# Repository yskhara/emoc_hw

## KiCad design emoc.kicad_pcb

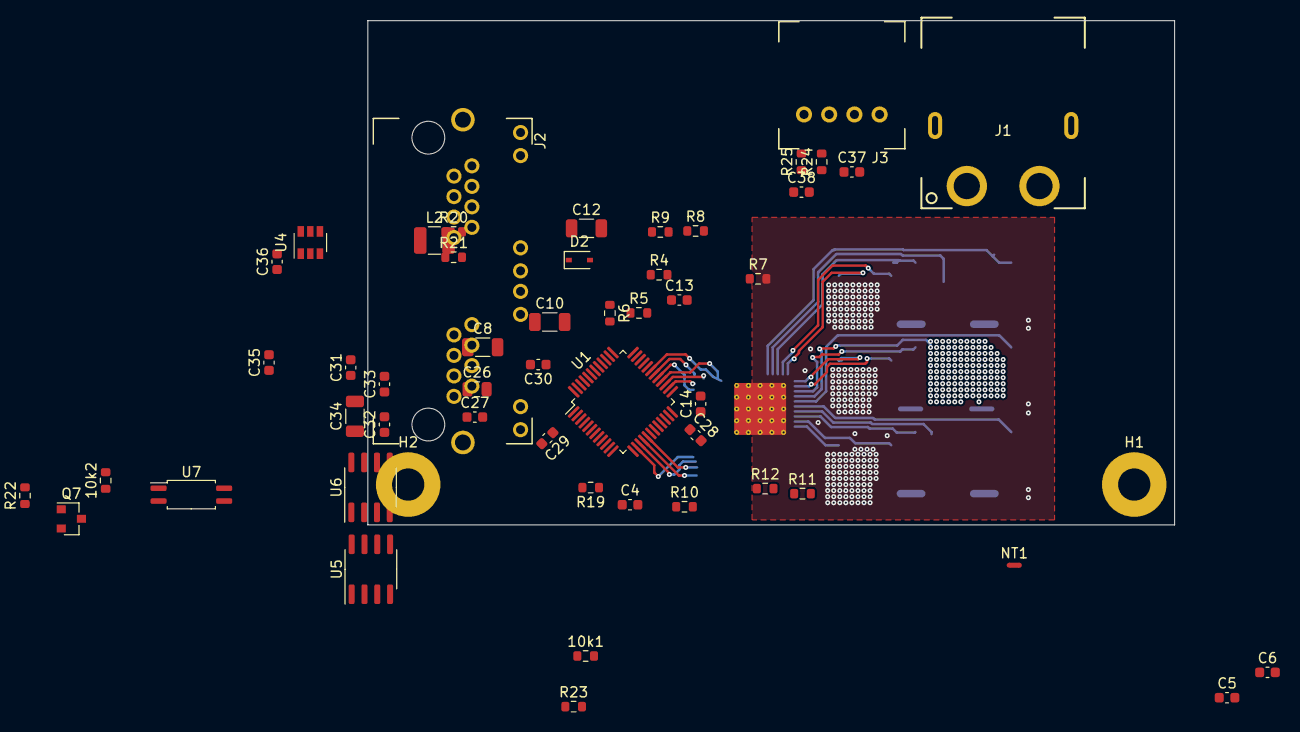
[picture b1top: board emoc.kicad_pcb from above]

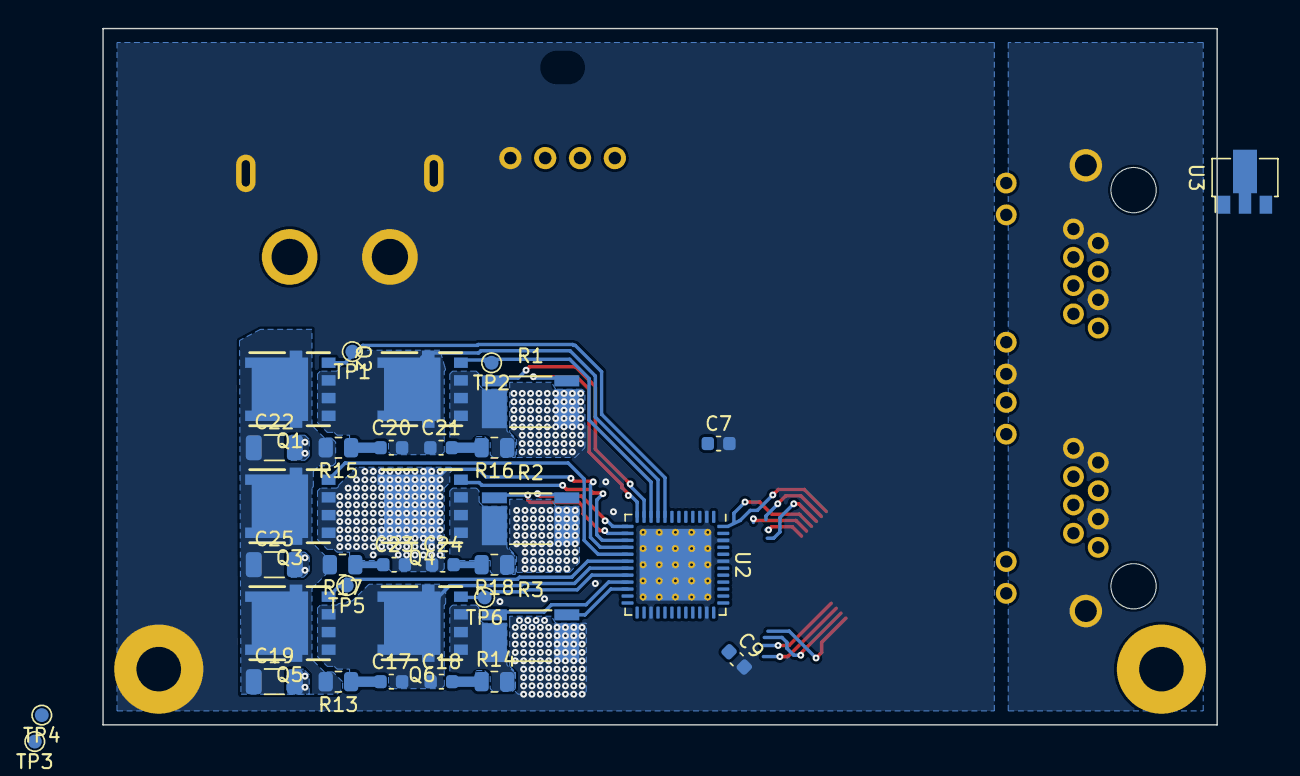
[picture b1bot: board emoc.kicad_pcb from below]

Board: 4 copper layers, 80.0 x 50.0 mm, 87 parts (34 on the bottom side), 81 nets.

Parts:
10k1, 10k2: R_US; R_0603_1608Metric
C4, C5, C6: TBD; C_0603_1608Metric
C7, C9, C14, C28, C29, C30, C31, C32, C33, C35, C36: 100n; C_0603_1608Metric
C8, C12, C34: 1u; C_1206_3216Metric
C10: 4.7uF; C_1206_3216Metric
C13: 47n; C_0603_1608Metric
C17, C18, C20, C21, C23, C24: 4n7; C_0603_1608Metric
C19, C22, C25: TBD; C_1206_3216Metric
C26: 1u; C_0805_2012Metric
C27: 10n; C_0603_1608Metric
C37, C38: 220p; C_0603_1608Metric
D2: PMEG6010CEJ,115; D_SOD-323
H1, H2: MountingHole_Pad; MountingHole_3.2mm_M3_Pad
J1: XT60PW-M
J2: RJHSE-x38x-02_CAN; RJHSE-x38x-02
J3: Conn_01x04; EP25_1744426-4
L2: L; L_1210_3225Metric
NT1: Net-Tie_2; NetTie-2_SMD_Pad0.5mm
Q1, Q2, Q3, Q4, Q5, Q6: NVMFS5C604NL; SO-8FL
Q7: BSS138; SOT-23
R1, R2, R3: R_Shunt_US; R_Shunt_2512
R4, R7, R19: 10k; R_0603_1608Metric
R5, R10, R11, R12: TBD; R_0603_1608Metric
R6, R8, R9: 54k9; R_0603_1608Metric
R13, R14, R15, R16, R17, R18: 10; R_0805_2012Metric
R20, R21: R_US; R_0603_1608Metric
R22, R24, R25: 100R; R_0603_1608Metric
R23: 51k1; R_0603_1608Metric
TP1, TP2, TP3, TP4, TP5, TP6: TestPoint; TestPoint_Pad_D1.0mm
U1: STM32F303CBTx; LQFP-48_7x7mm_P0.5mm
U2: DRV8323R; VQFN-48-1EP_7x7mm_P0.5mm_EP5.15x5.15mm_ThermalVias
U3: MC78L05_SOT89; SOT-89-3
U4: TPS562201; SOT-23-6
U5: Si8621AB-B-IS; SOIC-8_3.9x4.9mm_P1.27mm
U6: NCV7351D13; SOIC-8_3.9x4.9mm_P1.27mm
U7: TLP291; SOIC-4_4.55x2.6mm_P1.27mm

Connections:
+3V3: C28.1, C29.1, C30.1, R4.1, R19.2, U1.1, U1.24, U1.36, U1.48, U5.1, U7.4
+5V: J3.2, R6.1
+5VD: C33.1, C34.1, C35.1, C36.1, L2.2, R20.2, U3.1, U5.8, U6.3, U6.5
+12V: 10k2.2, C31.2, J2.1-4, J2.1-5, J2.2-4, J2.2-5, U3.3, U4.3, U4.5
/emoc_page3/SL_A: Q2.1, Q2.2, Q2.3, R1.1, R16.1
/emoc_page3/SL_B: Q4.1, Q4.2, Q4.3, R2.1, R18.1
/emoc_page3/SL_C: Q6.1, Q6.2, Q6.3, R3.1, R14.1
/emoc_page4/CAN_H: J2.1-1, J2.2-1, U6.7
/emoc_page4/CAN_L: J2.1-2, J2.2-2, U6.6
/emoc_page4/~EMS_ISO: J2.1-6, J2.2-6, R22.2, R23.1
CAN_RX: U1.45, U5.3
CAN_TX: U1.46, U5.2
DC_FB: R8.1, R9.2
ENC_A: C37.2, R24.1
ENC_B: C38.1, R25.1
FAULT: R4.2, U2.28
GH_A: Q1.4, TP1.1, U2.8
GH_B: Q3.4, TP3.1, U2.17
GH_C: Q5.4, TP5.1, U2.18
GL_A: Q2.4, TP2.1, U2.10
GL_B: Q4.4, TP4.1, U2.15
GL_C: Q6.4, TP6.1, U2.20
GND: 10k1.1, C4.2, C5.2, C6.2, C7.2, C8.2, C9.2, C10.2, C19.2, C22.2, C25.2, C26.2, C27.2, C28.2, C29.2, C30.2, C37.1, C38.2, H1.1, H2.1, J1.1, J1.3, J3.1, R1.4, R2.4, R3.4, R7.2, R9.1, U1.23, U1.35, U1.47, U2.2, U2.27, U2.35, U2.43, U2.46, U2.49, U5.4
GNDD: C31.1, C33.2, C34.2, C35.2, C36.2, J2.1-3, J2.1-7, J2.1-8, J2.2-3, J2.2-7, J2.2-8, J2.2-9, J2.S1, J2.S2, Q7.2, R21.1, R23.2, U3.2, U4.1, U5.5, U6.2, U6.8
IA: C6.1, R12.2
IB: C5.1, R11.2
IC: C4.1, R10.2
INH_A: U1.29, U2.37
INH_B: U1.30, U2.39
INH_C: U1.31, U2.41
INL_A: U1.26, U2.38
INL_B: U1.27, U2.40
INL_C: U1.28, U2.42
MISO: U1.16, U2.29
MOSI: U1.17, U2.30
unnamed: 10k2.1, U7.1
unnamed: C8.1, U2.36
unnamed: C7.1, C10.1, C12.1, D2.1, U2.6
unnamed: C12.2, U2.5
unnamed: C13.1, U2.4
unnamed: C13.2, U2.3
unnamed: C14.1, U2.44
unnamed: C14.2, U2.45
unnamed: C17.1, R13.1
unnamed: C18.2, R14.2
unnamed: C20.1, R15.1
unnamed: C21.2, R16.2
unnamed: C23.1, R17.1
unnamed: C24.2, R18.2
unnamed: C26.1, C27.1, U1.9
unnamed: C32.1, U4.6
unnamed: C32.2, L2.1, U4.2
unnamed: J2.1-9, J2.2-10
unnamed: J3.3, R24.2
unnamed: J3.4, R25.2
unnamed: NT1.1, U2.7
unnamed: Q7.1, R22.1
unnamed: Q7.3, U7.2
unnamed: R5.2, U2.48
unnamed: R6.2, R7.1, U2.1
unnamed: R10.1, U2.23
unnamed: R11.1, U2.24
unnamed: R12.1, U2.25
unnamed: R19.1, U1.7
unnamed: R20.1, R21.2, U4.4
unnamed: U5.6, U6.4
unnamed: U5.7, U6.1
SCK: U1.15, U2.31
SH_A: C20.2, C21.1, Q1.1, Q1.2, Q1.3, Q2.5, U2.9
SH_B: C23.2, C24.1, Q3.1, Q3.2, Q3.3, Q4.5, U2.16
SH_C: C17.2, C18.1, Q5.1, Q5.2, Q5.3, Q6.5, U2.19
SN_A: R1.3, U2.12
SN_B: R2.3, U2.13
SN_C: R3.3, U2.22
SP_A: R1.2, U2.11
SP_B: R2.2, U2.14
SP_C: R3.2, U2.21
VDC: C19.1, C22.1, C25.1, D2.2, J1.2, NT1.2, Q1.5, Q3.5, Q5.5, R5.1, R8.2, R13.2, R15.2, R17.2, U2.47
VDDA: C9.1, U2.26
~EMS: 10k1.2, U7.3
~SS: U1.14, U2.32

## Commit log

2020-10-02 change schdoc structure
2020-12-28 remove schdocs
2020-12-28 initial commit as kicad project
2020-12-28 remove backup file
2020-12-28 remove deprecated items
2021-01-02 still work in progress
